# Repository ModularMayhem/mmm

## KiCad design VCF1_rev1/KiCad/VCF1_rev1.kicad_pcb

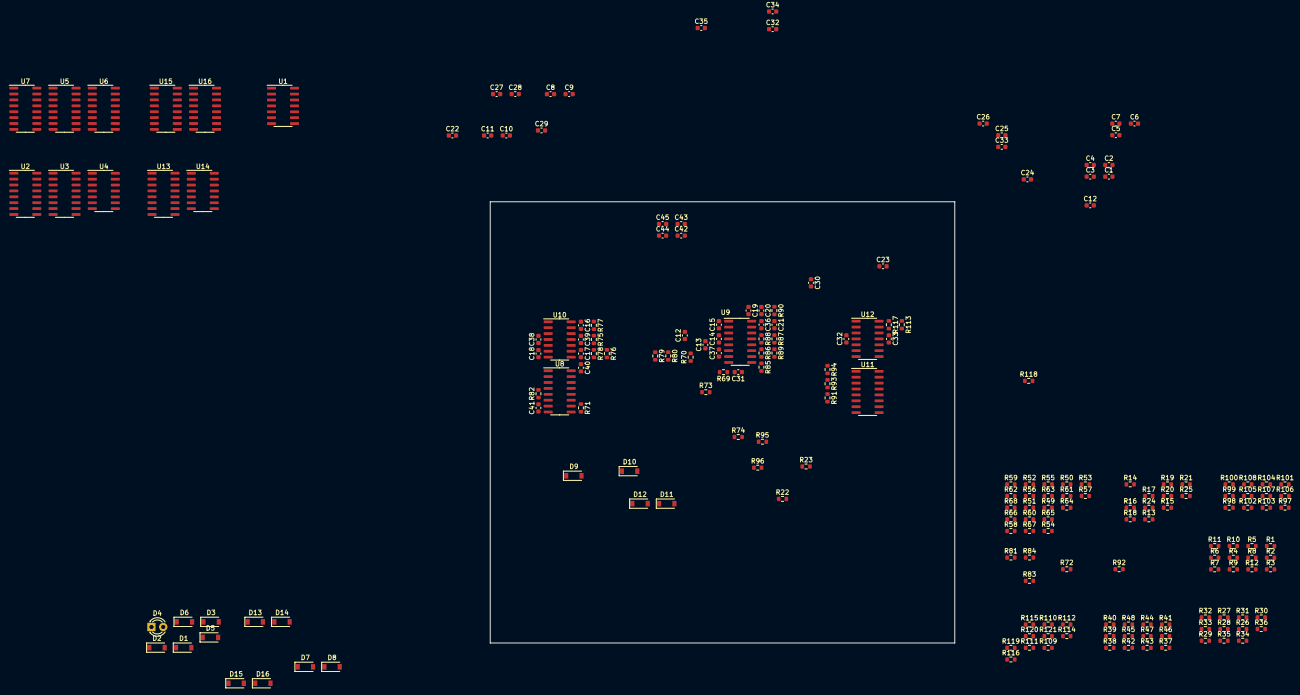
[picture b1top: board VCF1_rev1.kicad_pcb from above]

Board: 4 copper layers, 100.0 x 95.0 mm, 201 parts (0 on the bottom side), 128 nets, no tracks yet.

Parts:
C1, C2, C4: 47pF; C_0603_1608Metric
C3: 10pF; C_0603_1608Metric
C5, C13, C19, C24: 220pF; C_0603_1608Metric
C6, C14, C20, C25: 20nF; C_0603_1608Metric
C7, C15, C21, C26: 1nF; C_0603_1608Metric
C8, C9, C10, C11, C12, C12#2, C16, C17, C18, C22, C23, C27, C28, C29: C; C_0603_1608Metric
C30, C31, C32, C32#2, C33, C33#2, C34, C35, C36, C37, C38, C39, C40, C41, C42, C43, C44, C45: 100nF; C_0603_1608Metric
D1, D2, D3, D5, D6, D7, D8, D9, D10, D11, D12, D13, D14, D15, D16: D; D_SOD-123
D4: LED; LED_D3.0mm
R1, R2, R3, R4, R5, R6, R7, R8, R9, R10, R11, R12, R13, R14, R15, R16, R17, R18, R19, R20, R21, R22, R23, R24, R25, R42, R47, R48, R53, R55, R59, R60, R61, R62, R63, R64, R65, R66, R74, R79, R80, R90, R95, R96, R102, R107, R108, R109, R110, R111, R112, R113, R114, R115, R116, R117, R118, R119, R120, R121: R; R_0603_1608Metric
R26, R27, R28, R29, R30, R34, R35, R36, R49, R50, R82: 100kΩ; R_0603_1608Metric
R31, R41, R73, R89, R101: 330kΩ; R_0603_1608Metric
R32: 4k7Ω; R_0603_1608Metric
R33: TBD; R_0603_1608Metric
R37, R38, R69, R70, R85, R86, R97, R98: 200Ω; R_0603_1608Metric
R39, R54, R56, R71, R81, R83, R84, R87, R99: 10kΩ; R_0603_1608Metric
R40, R43, R44, R72, R75, R76, R88, R91, R92, R100, R103, R104: 220Ω; R_0603_1608Metric
R45, R46, R77, R78, R93, R94, R105, R106: 22kΩ; R_0603_1608Metric
R51, R52, R57, R58: 620Ω; R_0603_1608Metric
R67: 30kΩ; R_0603_1608Metric
R68: 1kΩ; R_0603_1608Metric
U1, U4, U10, U12, U14: Opamp_Quad; SOIC-14_3.9x8.7mm_P1.27mm
U2, U6, U7, U8, U11, U13, U15: 74HC4053; SOIC-16_3.9x9.9mm_P1.27mm
U3, U9: CEM3350; SOIC-16_3.9x9.9mm_P1.27mm
U5, U16: LM13700; SOIC-16_3.9x9.9mm_P1.27mm

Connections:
+10V: C30.1, C32.1, C32#2.1, C34.1, C36.1, C38.1, C40.2, C41.1, C44.1, R54.1, R56.1, R115.1, U1.4 (V+), U3.16 (Vcc), U4.4 (V+), U8.16 (Vcc), U9.16 (Vcc), U10.4 (V+), U11.16 (Vcc), U12.4 (V+)
-10V: C31.2, C33.2, C33#2.2, C35.2, C37.2, C39.1, C42.2, C43.2, C45.2, R68.2, R121.2, U1.11 (V-), U3.7 (Vee), U4.11 (V-), U8.7 (Vee), U9.7 (Vee), U10.11 (V-), U11.7 (Vee), U12.11 (V-)
/Audiopanel/Audio_out: C4.2, R36.1, U1.14, U2.14 (X)
/Audiopanel/Input_3: D1.1 (K), R32.1, R35.1
/CVpanel/Frequency_sum_VCF1: R1.2, R5.1, R9.1, R37.1, U3.8 (Vcf)
/CVpanel/Frequency_sum_VCF2: R2.2, R6.1, R10.1
/CVpanel/Frequency_sum_VCF3: R3.2, R7.1, R11.1
/CVpanel/Frequency_sum_VCF4: R4.2, R8.1, R12.1, R97.1, U3.10 (Vcf)
/CVpanel/Resonance_sum_VCF1: R38.1, U3.6 (Vcq)
/CVpanel/Resonance_sum_VCF4: R98.1, U3.11 (Vcq)
/Controlpanel/Feedback_select: R20.1, U6.11 (A)
/Controlpanel/Parallel_select: R21.1, U6.9 (C), U6.10 (B), U7.11 (A)
/Controlpanel/Ring_modulator_select: R19.1, U13.9 (C), U15.10 (B), U15.11 (A)
/Controlpanel/VCF1_HP_select: R13.1, U2.10 (B)
/Controlpanel/VCF1_LP_select: R15.1, U2.11 (A)
/Controlpanel/VCF2_HP_select: R14.1, U8.11 (A)
/Controlpanel/VCF2_LP_select: R16.1, U8.1 (Y1)
/Controlpanel/VCF2_invert_select: R17.1, U8.9 (C)
/Controlpanel/VCF2_overdrive_select: R18.1, U2.9 (C)
/Controlpanel/VCF3_HP_select: R22.1, U11.9 (C)
/Controlpanel/VCF3_LP_select: R23.1, U11.10 (B)
/Controlpanel/VCF4_HP_select: R24.1, U13.10 (B)
/Controlpanel/VCF4_LP_select: R25.1, U13.11 (A)
/MUX/Audio_in: U2.15 (Y), U6.1 (Y1), U6.5 (Z0), U6.12 (X0)
/MUX/Audio_out: U7.14 (X), U13.14 (X)
/MUX/Mixer_out: R67.1, U5.5, U5.10, U5.12, U6.2 (Y0)
/MUX/VCF2_return: C18.1, D11.1 (K), D12.2 (A), R49.1, R83.2, R84.2, U10.7
/MUX/VCF2_send: U6.14 (X), U8.2 (Y0)
/MUX/VCF3_return: U6.3 (Z1), U6.13 (X1), U7.12 (X0), U11.4 (Z)
/MUX/VCF3_send: U6.15 (Y), U11.15 (Y)
/Power/Iref: U3.1 (Iref), U9.1 (Iref)
/VCA/Audio_in: R110.1, U13.3 (Z1), U13.15 (Y), U15.13 (X1)
/VCA/Audio_out: R121.1, U16.9
/VCF_2/VCF2_HP_out: C17.2, R73.2, R78.2, R79.2, U8.13 (X1), U10.8
/VCF_2/VCF2_LP_BP_out: C16.1, R77.1, U8.12 (X0), U10.14
/VCF_3/VCF3_HP_out: C23.2, R89.2, R94.2, R95.2, U11.3 (Z1), U12.7
/VCF_3/VCF3_LP_BP_out: C22.2, R93.2, U11.5 (Z0), U12.1
GND: C6.2, C14.2, C20.1, C25.2, C30.2, C31.1, C32.2, C32#2.2, C33.1, C33#2.1, C34.2, C35.1, C36.2, C37.1, C38.2, C39.2, C40.1, C41.2, C42.1, C43.1, C44.2, C45.1, D3.2 (A), D6.1 (K), R13.2, R14.2, R15.2, R16.2, R17.2, R18.2, R19.2, R20.2, R21.2, R22.2, R23.2, R24.2, R25.2, R32.2, R37.2, R38.2, R40.2, R42.2, R43.2, R44.2, R48.2, R51.2, R52.2, R57.2, R58.2, R59.2, R60.2, R67.2, R69.2, R70.1, R72.2, R74.2, R75.2, R76.2, R80.2, R82.1, R85.2, R86.2, R88.1, R90.1, R91.2, R92.2, R96.2, R97.2, R98.2, R100.2, R102.2, R103.2, R104.2, R108.2, R112.2, R113.2, R116.2, U1.3 (+), U1.5 (+), U1.10 (+), U1.12 (+), U3.4 (Viv), U3.9 (GND), U3.14 (Viv), U5.7, U8.6 (~E), U8.8 (GND), U9.4 (Viv), U9.9 (GND), U9.14 (Viv), U11.6 (~E), U11.8 (GND), U15.12 (X0)
unnamed: C1.1, R26.1, R29.2, U1.2 (-)
unnamed: C1.2, R29.1, U1.1
unnamed: C2.1, R27.1, R30.2, U1.6 (-)
unnamed: C2.2, R30.1, U1.7
unnamed: C3.1, R28.1, R31.2, U1.9 (-)
unnamed: C3.2, R31.1, U1.8
unnamed: C4.1, R34.2, R35.2, R36.2, U1.13 (-)
unnamed: C5.1, U2.12 (X0)
unnamed: C5.2, C6.1, U3.5 (Vbp), U4.5 (+)
unnamed: C7.1, D7.1 (K), D8.2 (A), R42.1
unnamed: C7.2, U3.3 (Vlp), U4.3 (+)
unnamed: C8.1, R43.1, R45.1, U4.2 (-)
unnamed: C8.2, R45.2, U2.2 (Y0), U4.1
unnamed: C9.1, R44.1, R46.1, U4.6 (-)
unnamed: C9.2, R41.2, R46.2, R47.2, U2.1 (Y1), U4.7
unnamed: C10.1, R59.1, R61.1, U4.9 (-)
unnamed: C10.2, R61.2, R65.1, U4.8
unnamed: C11.1, R60.1, R63.1, U4.13 (-)
unnamed: C11.2, R63.2, R66.1, U4.14
unnamed: C12.1, C12#2.1, R68.1, U5.9
unnamed: C12.2, C12#2.2, U7.13 (X1)
unnamed: C13.1, C14.1, U9.5 (Vbp), U10.10 (+)
unnamed: C13.2, U8.15 (Y)
unnamed: C15.1, U9.3 (Vlp), U10.12 (+)
unnamed: C15.2, D9.1 (K), D10.2 (A), R74.1
unnamed: C16.2, R75.1, R77.2, U10.13 (-)
unnamed: C17.1, R76.1, R78.1, U10.9 (-)
unnamed: C18.2, U2.4 (Z), U10.6 (-)
unnamed: C19.1, U11.2 (Y0)
unnamed: C19.2, C20.2, U9.15 (Vbp), U12.5 (+)
unnamed: C21.2, U9.13 (Vlp), U12.3 (+)
unnamed: C22.1, R91.1, R93.1, U12.2 (-)
unnamed: C23.1, R92.1, R94.1, U12.6 (-)
unnamed: C24.1, U13.12 (X0)
unnamed: C24.2, C25.1, U3.15 (Vbp), U14.5 (+)
unnamed: C26.1, D15.1 (K), D16.2 (A), R102.1
unnamed: C26.2, U3.13 (Vlp), U14.3 (+)
unnamed: C27.1, R103.1, R105.1, U14.2 (-)
unnamed: C27.2, R105.2, U13.2 (Y0), U14.1
unnamed: C28.1, R104.1, R106.1, U14.6 (-)
unnamed: C28.2, R101.2, R106.2, R107.2, U13.1 (Y1), U14.7
unnamed: C29.1, R114.2, R118.1, U12.12 (+)
unnamed: C29.2, R117.1, R119.1, U12.14
unnamed: D1.2 (A), D2.1 (K)
unnamed: D2.2 (A), D3.1 (K)
unnamed: D4.1 (K), R33.1
unnamed: D5.1 (K), D6.2 (A)
unnamed: D7.2 (A), D8.1 (K), R47.1, R48.1
unnamed: D9.2 (A), D10.1 (K), R79.1, R80.1
unnamed: D11.2 (A), D12.1 (K), U2.3 (Z1)
unnamed: C21.1, D13.1 (K), D14.2 (A), R90.2
unnamed: D13.2 (A), D14.1 (K), R95.1, R96.1
unnamed: D15.2 (A), D16.1 (K), R107.1, R108.1
unnamed: R1.1, R2.1, R3.1, R4.1
unnamed: R39.1, U2.13 (X1)
unnamed: R39.2, R40.1, R41.1, U3.2 (Vif)
unnamed: R49.2, R57.1, U5.14 (+)
unnamed: R50.1, U6.4 (Z)
unnamed: R50.2, R58.1, U5.3 (+)
unnamed: R51.1, U5.13 (-)
unnamed: R52.1, U5.4 (-)
unnamed: R53.2, R62.1, U4.10 (+)
unnamed: R54.2, U5.15 (DIODE_BIAS)
unnamed: R55.2, R64.1, U4.12 (+)
unnamed: R56.2, U5.2 (DIODE_BIAS)
unnamed: R62.2, R65.2, U5.16
unnamed: R64.2, R66.2, U5.1
unnamed: R69.1, U9.8 (Vcf)
unnamed: R70.2, U9.6 (Vcq)
unnamed: R71.1, U8.10 (B)
unnamed: R71.2, R72.1, R73.1, U9.2 (Vif)
unnamed: R81.1, U8.5 (Z0), U8.14 (X)
unnamed: R81.2, R83.1
unnamed: R82.2, U8.4 (Z), U10.5 (+)
unnamed: R84.1, U2.5 (Z0)
unnamed: R85.1, U9.10 (Vcf)
unnamed: R86.1, U9.11 (Vcq)
unnamed: R87.1, U11.1 (Y1)
unnamed: R87.2, R88.2, R89.1, U9.12 (Vif)
unnamed: R99.1, U13.13 (X1)
unnamed: R99.2, R100.1, R101.1, U3.12 (Vif)
unnamed: R109.1, U15.1 (Y1)
unnamed: R110.2, R111.2, R112.1, U16.13 (-)
unnamed: R111.1, U13.4 (Z)
unnamed: R113.1, R117.2, U12.13 (-), U15.15 (Y)
unnamed: R115.2, U16.15 (DIODE_BIAS)
unnamed: R116.1, U16.14 (+)
unnamed: R118.2, R119.2, U16.16
unnamed: R120.1, U16.10, U16.12
unnamed: R120.2, U15.14 (X)

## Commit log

2021-10-07 First commit of VCF1. Empty project, just to get started.
2021-10-07 First draft of the filter core. Also changed the directory structure a bit.
2021-10-07 Added LP/BP/HP and serial/parallel muxes.
2021-10-08 Just some notes so I don't forget about something.
2021-10-08 Added tip from Sjoerd about regulators.
2021-10-08 Another thought: Should it be possible to select just one filter?
2021-10-08 Quick renaming of the files since the MM- prefix was not meant to be copied.
2021-10-08 Shifted to multi page layout and also started on the panel.
2021-10-08 Added some initial resonance control and some other stuff.
2021-10-08 Forgot to update the pfd.
2021-10-12 First version of some kind of functional documentation of the filter.
2021-10-14 Added a VCA for VCF2 and cleaned up the drawings a bit.
2021-10-18 Moved over to KiCad 5.99, recadded CEM3350-module and created the input mixer.
2021-10-31 A lot of work especially on VCF2. Doc updated. Schematics a bit in a flux due to major restructuring.
2021-11-07 Added VCA (with a quirk) and also drew a new symbol for 74HC4053 because the standard one annoyed me.
2021-11-07 Cleaned up the VCF2 schematics.
2021-11-08 The filter blocks are more or less done, page order has gotten more sane for easier reading.
2021-11-09 Added the MUX. The signal path is now more or less complete!
2021-11-22 Lot of work on panel etc.
2021-11-23 Cleaned up the first page with the overview and tried to make it a bit more readable.
2021-11-24 Drew a better symbol for LM13700 because the other one was ugly.
2021-11-26 Cleanups, better names for the sheets etc.
2021-12-02 Started to populate the PCB and done some small fixes in the schematics.
2021-12-04 Placed more components on the PCB.
